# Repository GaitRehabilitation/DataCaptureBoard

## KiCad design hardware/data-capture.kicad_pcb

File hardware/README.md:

## devices

- [LSF0108](http://www.ti.com/lit/ds/symlink/lsf0102.pdf)

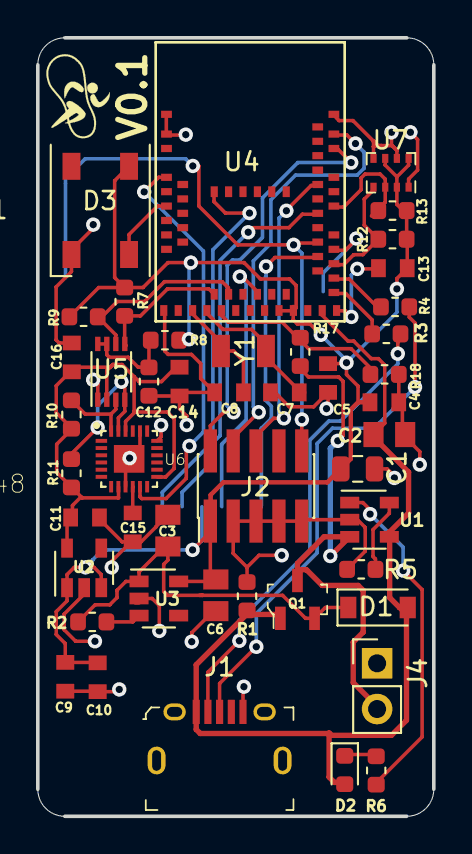
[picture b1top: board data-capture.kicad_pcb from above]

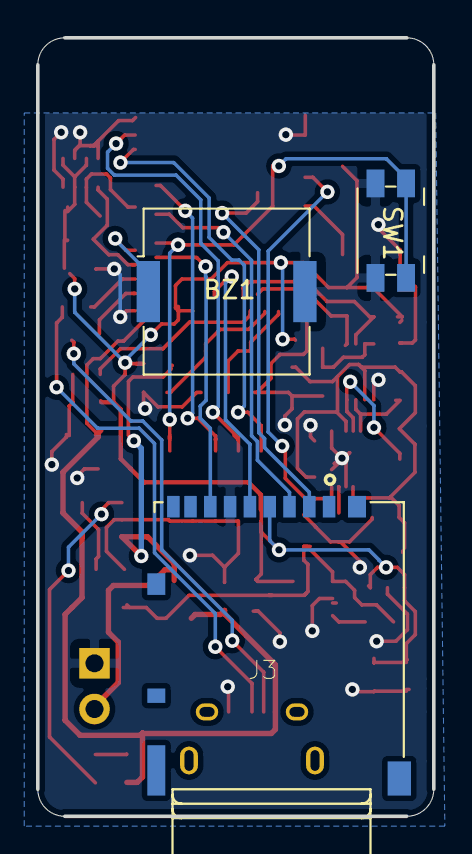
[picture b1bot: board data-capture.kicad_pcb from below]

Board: 2 copper layers, 22.0 x 43.2 mm, 49 parts (3 on the bottom side), 36 nets.

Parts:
BZ1: Buzzer; Buzzer_Murata_PKMCS0909E4000-R1
C1, C2, C3, C6: 10uF; C_0805_2012Metric
C4, C5, C9, C13, C14, C15, C16: .1uF; C_0603_1608Metric
C7, C8: 12pF; C_0603_1608Metric
C10, C11: 1uF; C_0603_1608Metric
C12: 100PF; C_0603_1608Metric
D1: D_Schottky; D_SOD-123
D2: LED; D_0603_1608Metric
D3: WS2812B; LED_WS2812B_PLCC4_5.0x5.0mm_P3.2mm
J1: USB_B_Mini; USB_Micro_B_Female_10118194-0001LF
J2: Conn_ARM_JTAG_SWD_10-Connector_Specialized-bed-se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; PinHeader_2x05_P1.27mm_Vertical_SMD
J3: DM3AT-SF-PEJM5; HRS_DM3AT-SF-PEJM5
J4: Conn_01x02; PinHeader_1x02_P2.54mm_Vertical
Q1: Q_PMOS_GSD; SOT-23-3
R1, R2, R17, R18: 100K; R_0603_1608Metric
R3, R4: 22; R_0603_1608Metric
R5, R7, R9, R10, R11, R12, R13: 4.7K; R_0603_1608Metric
R6: 1K; R_0603_1608Metric
R8: 200k; R_0603_1608Metric
SW1: SW_Push; Panasonic_EVQPUJ_EVQPUA
U1: MCP73831-2-OT; SOT-23-5
U2: TLV70218_SOT23-5; SOT-23-5
U3: AP2112K-3.3; SOT-23-5
U4: MDBT50Q-1M
U5: PCA9306; VSSOP-8_2.3x2mm_P0.5mm
U6: ICM-20948
U7: BMP280; Bosch_LGA-8_2x2.5mm_P0.65mm_ClockwisePinNumbering
Y1: 32.768; FC-135 32.7680KA-AC3

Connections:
+1V8: C11.1, C14.2, C16.2, R10.2, R11.2, U2.5, U5.2, U6.8, U6.13, U6.22
+3V3: C1.1, C4.1, C5.1, C6.1, C9.1, C10.1, C13.2, D3.1, J2.1, J3.4, R7.2, R8.2, R9.2, R12.2, R13.2, U2.1, U2.3, U3.5, U4.28, U4.30, U7.2, U7.6, U7.8
+BATT: J4.2, Q1.3, R17.1, U1.3
BMP_SCL: R12.1, U4.37, U7.4
BMP_SDA: R13.1, U4.44, U7.3
BUZZER: BZ1.1, U4.39
GND: BZ1.2, C1.2, C2.2, C3.2, C4.2, C5.2, C6.2, C7.2, C8.2, C9.2, C10.2, C11.2, C12.2, C13.1, C14.1, C15.1, C16.1, D3.3, J1.5, J2.3, J2.5, J2.7, J2.9, J3.6, J4.1, R1.2, R5.2, R18.2, SW1.2, U1.2, U2.2, U3.2, U4.1, U4.2, U4.15, U4.33, U4.55, U5.1, U6.9, U6.18, U6.20, U6.25, U7.1, U7.5, U7.7
IMU_FSYC: U4.4, U6.11
NEO_LED: D3.4, U4.8
unnamed: C3.1, D1.1, Q1.2, R2.2, U3.1
unnamed: C7.1, U4.18, Y1.1
unnamed: C8.1, U4.17, Y1.2
unnamed: C12.1, R8.1, U5.7, U5.8
unnamed: C15.2, U6.10
unnamed: D2.1, R6.2
unnamed: R2.1, U3.3
unnamed: R3.2, U4.34
unnamed: R4.2, U4.35
unnamed: R5.1, U1.5
unnamed: R6.1, U1.1
unnamed: R10.1, U5.3, U6.24
unnamed: R11.1, U5.4, U6.23
RESET: J2.10, SW1.1, U4.40
SCL_MPU: R7.1, U4.19, U5.5
SDA_MPU: R9.1, U4.21, U5.6
SD_CS: J3.2, U4.56
SD_MISO: J3.7, U4.38
SD_MOSI: J3.3, U4.43
SD_SCK: J3.5, U4.25
SWCLK: J2.4, U4.53
SWDIO: J2.2, U4.51
SWO: J2.6, U4.47
USB_D+: J1.3, R4.1
USB_D-: J1.2, R3.1
VBUS: C2.1, D1.2, D2.2, J1.1, Q1.1, R1.1, U1.4, U4.32
VDIV: R17.2, R18.1, U4.20

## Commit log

2019-06-20 added readme
2019-06-20 added firmware and hardware
2019-06-25 added flutter and started working on store for sd
2019-06-26 updated store
2019-06-27 added device firmware
2019-06-27 started on bluetooth
2019-06-28 started working on logger gatt protocol
2019-07-11 added logger code and started finish up bluetooth API
2019-07-11 added logger firmware
2019-07-11 added config
2019-07-17 added redux implemented pages
2019-07-18 added redux and react and updated app
2019-07-18 fixed dts for sdhc
2019-07-19 updated capture for app
2019-07-19 added expandable card
2019-07-20 updated presentation
2019-07-21 added app and basic working model for firmware
2019-07-24 added a not logging flag and reworked UI
2019-07-24 added close flasg to logger
2019-07-24 cleaned up firmware
2019-07-25 cleaned up firmware code and added example capture
2019-07-26 updated fimrware code
2020-06-17 update schematic for ESYNC for IMU
